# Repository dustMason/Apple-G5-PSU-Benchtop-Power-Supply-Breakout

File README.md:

Based on the open source [Benchtop Power product from Sparkfun](https://www.sparkfun.com/products/12867) and uses the same materials, except for an additional 16-pin molex connector to go along with the 24-pin one. Thanks for sharing, Sparkfun! I resized the board to fit within the limits of Eagle's free light version.

As you'll see, the only thing used on the 24 pin connector are the GND connections, the -12V power and the power switch, so that could be eliminated with some simple wiring when installing the board.

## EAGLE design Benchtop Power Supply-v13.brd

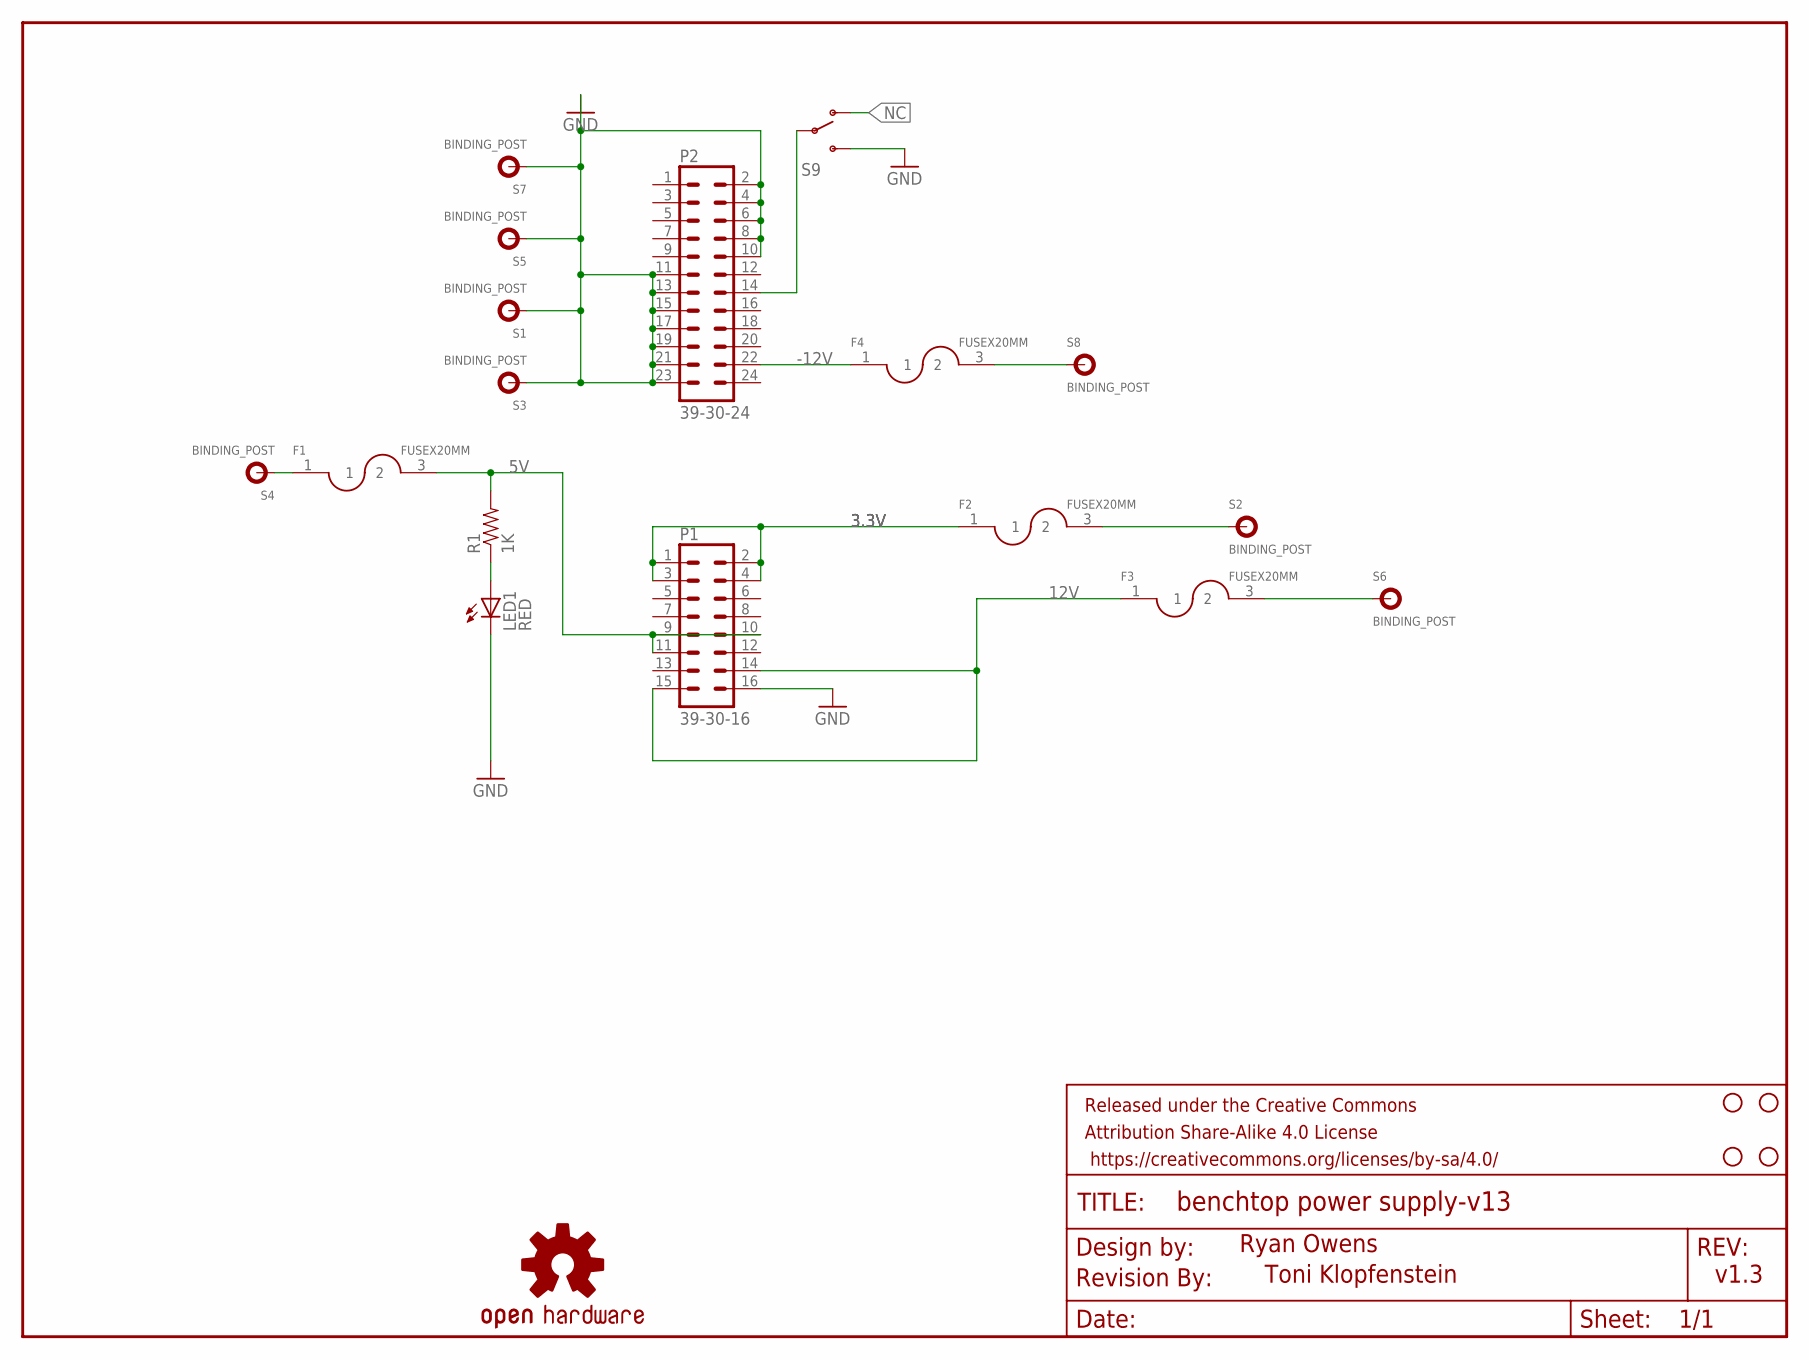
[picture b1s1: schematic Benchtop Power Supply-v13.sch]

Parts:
F1, F2, F3, F4: FUSEX20MM; FUSE_5MM
FRAME1: FRAME-LETTER; CREATIVE_COMMONS
JP2, JP3, JP4, JP5: STAND-OFF
LED1: RED; LED5MM
LOGO1: OSHW-LOGOL; OSHW-LOGO-L
P1: 39-30-16; 39-30-?16?
P2: 39-30-24; 39-30-?24?
R1: 1K; AXIAL-0.3
S1, S2, S3, S4, S5, S6, S7, S8: BINDING_POST
S9: SWITCH-SPDTKIT; SWITCH-SPDT_KIT
U$1: REVISION

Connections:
3.3V: F2.1, P1.1, P1.2, P1.3, P1.4
3.3V_P: F2.3 (2), S2.P$1
5V: F1.3 (2), P1.9, P1.10, P1.11, R1.P$2 (2)
5V_P: F1.1, S4.P$1
12V: F3.1, P1.14, P1.15
12V_P: F3.3 (2), S6.P$1
-12V: F4.1, P2.22
-12V_P: F4.3 (2), S8.P$1
GND: LED1.K (C), P1.16, P2.2, P2.4, P2.6, P2.8, P2.10, P2.11, P2.13, P2.15, P2.17, P2.19, P2.21, P2.23, S1.P$1, S3.P$1, S5.P$1, S7.P$1, S9.3 (S)
unnamed: LED1.A, R1.P$1 (1)
unnamed: P2.14, S9.2
NC: S9.1 (O)

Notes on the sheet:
Ryan Owens
Toni Klopfenstein
v1.3

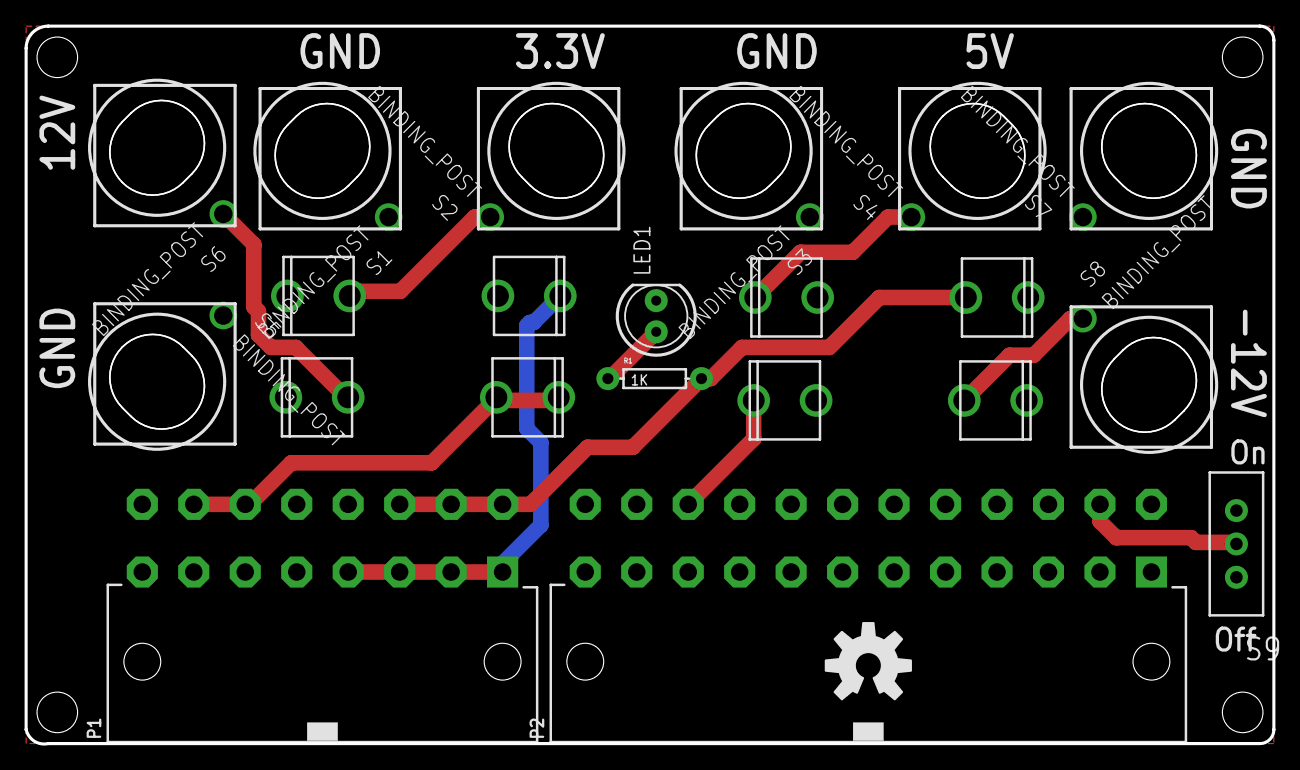
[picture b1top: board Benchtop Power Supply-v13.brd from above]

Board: 2 copper layers, 101.6 x 58.5 mm, 24 parts (0 on the bottom side), 11 nets.

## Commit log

2015-04-29 Init Commit
2015-04-29 Add image of board
2015-04-29 readme
2015-04-29 more readme
2015-04-29 yet more readme

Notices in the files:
parts and their libraries:
SparkFun-Connectors: Licensing: Creative Commons ShareAlike 4.0 International - https://creativecommons.org/licenses/by-sa/4.0
SparkFun-Aesthetics: Released under the Creative Commons Attribution Share-Alike 4.0 License
SparkFun-Aesthetics: https://creativecommons.org/licenses/by-sa/4.0
